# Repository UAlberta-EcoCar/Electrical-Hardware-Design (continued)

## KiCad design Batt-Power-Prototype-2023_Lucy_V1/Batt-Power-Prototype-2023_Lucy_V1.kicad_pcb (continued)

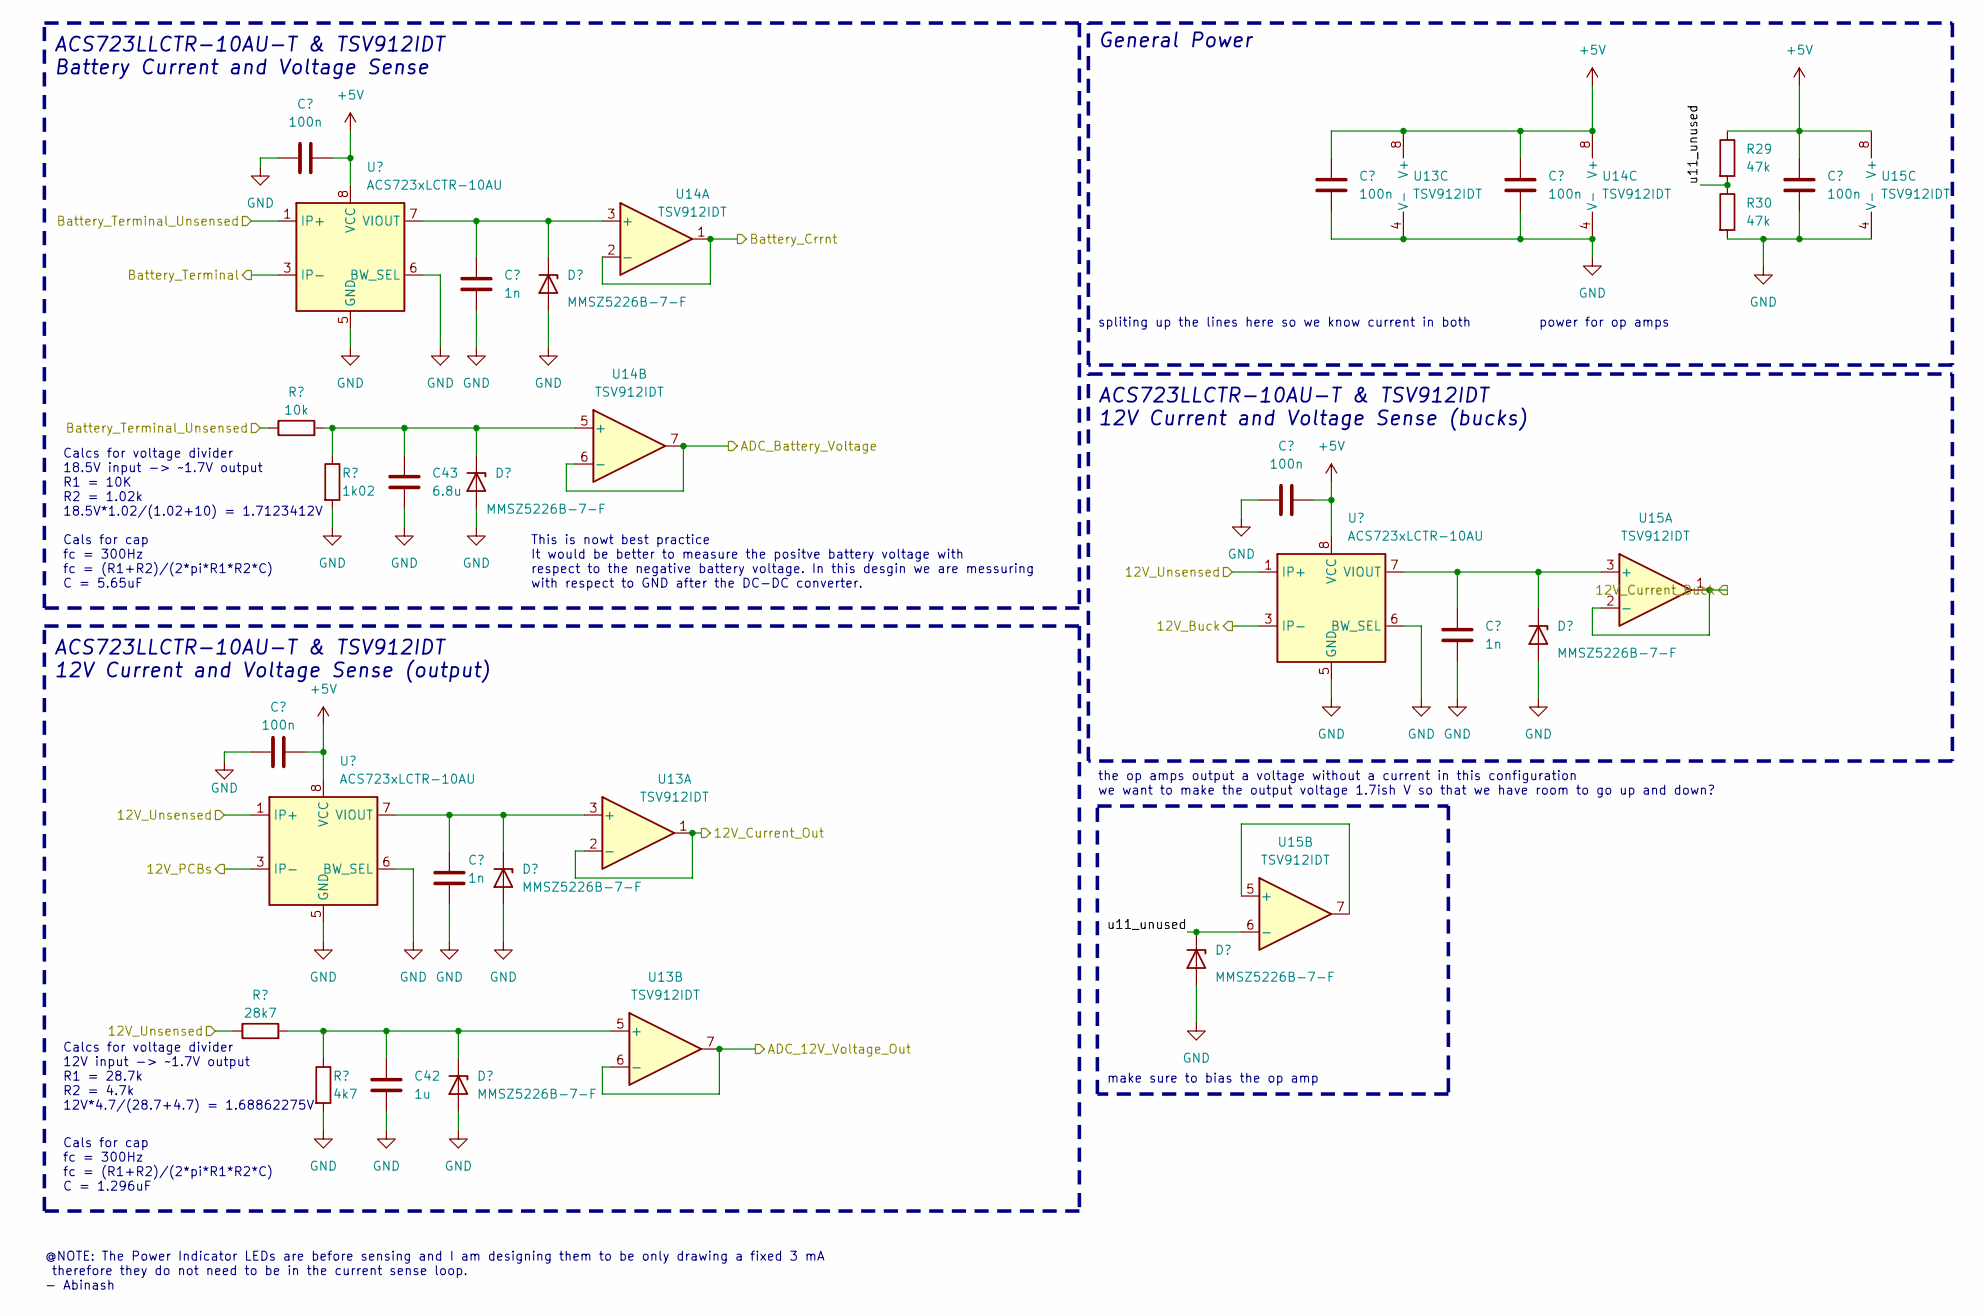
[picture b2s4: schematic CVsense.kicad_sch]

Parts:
C40, C46, C47, C49, C50: 100n; C_0603_1608Metric; Digikey # CC0603KRX7R7BB104
C41: 100n; C_0402_1005Metric; JLCPCB Part#(Optional) C1525
C42: 1u; C_0603_1608Metric; JLCPCB Part#(Optional) C28323
C43: 6.8u; C_0603_1608Metric; JLCPCB Part#(Optional) C1631
C44, C45, C48: 1n; C_0402_1005Metric; JLCPCB Part#(Optional) C1523
D16, D17, D18, D19, D20, D21: MMSZ5226B-7-F; D_SOD-123; Digikey # MMSZ5226B-FDICT-ND
R25: 28k7; R_0603_1608Metric; Digikey # RMCF0603FT28K7CT-ND
R26: 10k; R_0603_1608Metric; JLCPCB Part#(Optional) C25804
R27: 4k7; R_0603_1608Metric; JLCPCB Part#(Optional) C23164
R28: 1k02; R_0603_1608Metric; Digikey # RMCF0603FT1K02CT-ND
R29, R30: 47k; R_0805_2012Metric; JLCPCB Part#(Optional) C17713
U11, U12, U16: ACS723xLCTR-10AU; SOIC-8_3.9x4.9mm_P1.27mm
U13, U14, U15: TSV912IDT; SO8_STM; Digikey # 497-8165-2-ND

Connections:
+5V: C40.1, C41.2, C46.2, C47.1, C49.1, C50.1, R29.1, U11.8 (VCC), U12.8 (VCC), U13.8 (V+), U14.8 (V+), U15.8 (V+), U16.8 (VCC); also elsewhere on the board
/12V_Current_Buck: U15.1, U15.2 (-); also elsewhere on the board
/12V_Current_Out: U13.1, U13.2 (-); also elsewhere on the board
/ADC_12V_Voltage_Out: U13.6 (-), U13.7; also elsewhere on the board
/ADC_Battery_Voltage: U14.6 (-), U14.7; also elsewhere on the board
/Battery_Curr: U14.1, U14.2 (-); also elsewhere on the board
/Power/12V_Buck: U16.3 (IP-), U16.4 (IP-); also elsewhere on the board
/Power/12V_PCBs: U11.3 (IP-), U11.4 (IP-); also elsewhere on the board
/Power/12V_Unsensed: R25.1, U11.1 (IP+), U11.2 (IP+), U16.1 (IP+), U16.2 (IP+); also elsewhere on the board
/Power/Battery_Terminal_1: U12.3 (IP-), U12.4 (IP-); also elsewhere on the board
/Power/Battery_Terminal_1_Unsensed: R26.1, U12.1 (IP+), U12.2 (IP+); also elsewhere on the board
/Power/Current & Voltage Senseing/u11_unused: D20.1 (K), R29.2, R30.1, U15.6 (-)
GND: C40.2, C41.1, C42.2, C43.2, C44.2, C45.2, C46.1, C47.2, C48.2, C49.2, C50.2, D16.2 (A), D17.2 (A), D18.2 (A), D19.2 (A), D20.2 (A), D21.2 (A), R27.2, R28.2, R30.2, U11.5 (GND), U11.6 (BW_SEL), U12.5 (GND), U12.6 (BW_SEL), U13.4 (V-), U14.4 (V-), U15.4 (V-), U16.5 (GND), U16.6 (BW_SEL); also elsewhere on the board
unnamed: C42.1, D16.1 (K), R25.2, R27.1, U13.5 (+)
unnamed: C43.1, D17.1 (K), R26.2, R28.1, U14.5 (+)
unnamed: C44.1, D18.1 (K), U11.7 (VIOUT), U13.3 (+)
unnamed: C45.1, D19.1 (K), U12.7 (VIOUT), U14.3 (+)
unnamed: C48.1, D21.1 (K), U15.3 (+), U16.7 (VIOUT)
unnamed: U15.5 (+), U15.7

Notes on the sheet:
Cals for cap fc = 300Hz fc = (R1+R2)/(2*pi*R1*R2*C) C = 5.65uF
make sure to bias the op amp
the op amps output a voltage without a current in this configuration we want to make the output voltage 1.7ish V so that we have room to go up and down?
Calcs for voltage divider 12V input -> ~1.7V output R1 = 28.7k R2 = 4.7k 12V*4.7/(28.7+4.7) = 1.68862275V
General Power
ACS723LLCTR-10AU-T & TSV912IDT Battery Current and Voltage Sense
This is nowt best practice It would be better to measure the positve battery voltage with respect to the negative battery voltage. In this desgin we are messuring with respect to GND after the DC-DC converter.
Calcs for voltage divider 18.5V input -> ~1.7V output R1 = 10K R2 = 1.02k 18.5V*1.02/(1.02+10) = 1.7123412V
ACS723LLCTR-10AU-T & TSV912IDT 12V Current and Voltage Sense (output)
ACS723LLCTR-10AU-T & TSV912IDT 12V Current and Voltage Sense (bucks)
spliting up the lines here so we know current in both
power for op amps
Cals for cap fc = 300Hz fc = (R1+R2)/(2*pi*R1*R2*C) C = 1.296uF
@NOTE: The Power Indicator LEDs are before sensing and I am designing them to be only drawing a fixed 3 mA therefore they do not need to be in the current sense loop. - Abinash

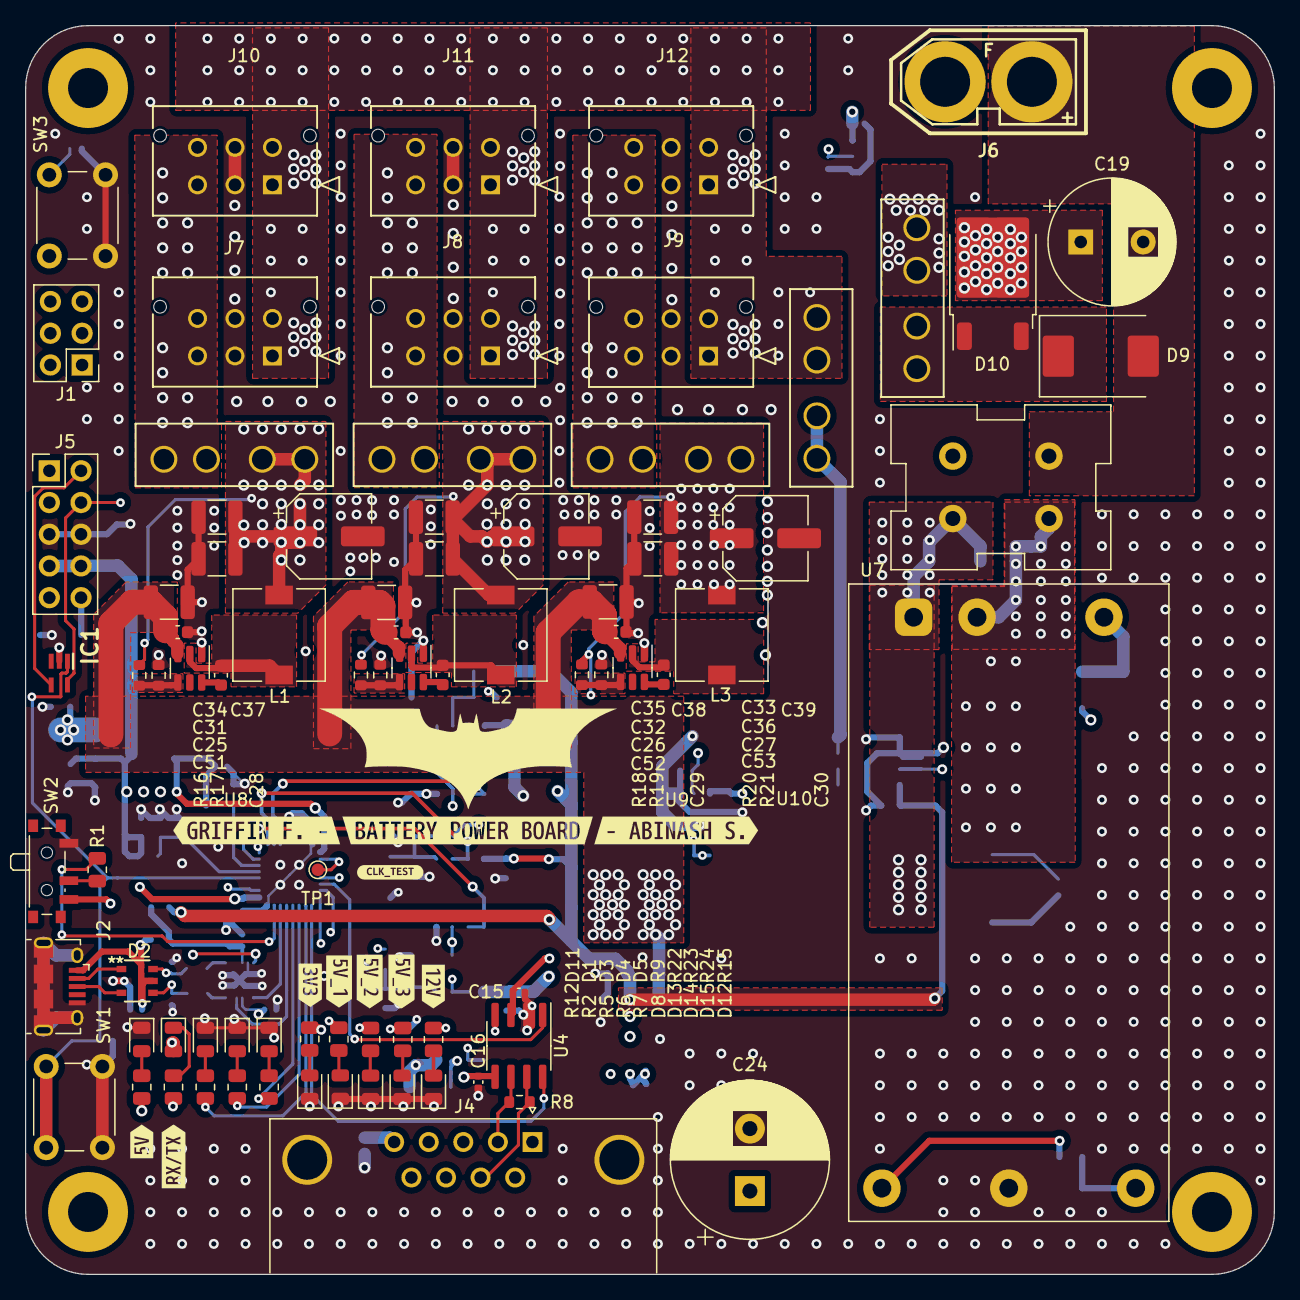
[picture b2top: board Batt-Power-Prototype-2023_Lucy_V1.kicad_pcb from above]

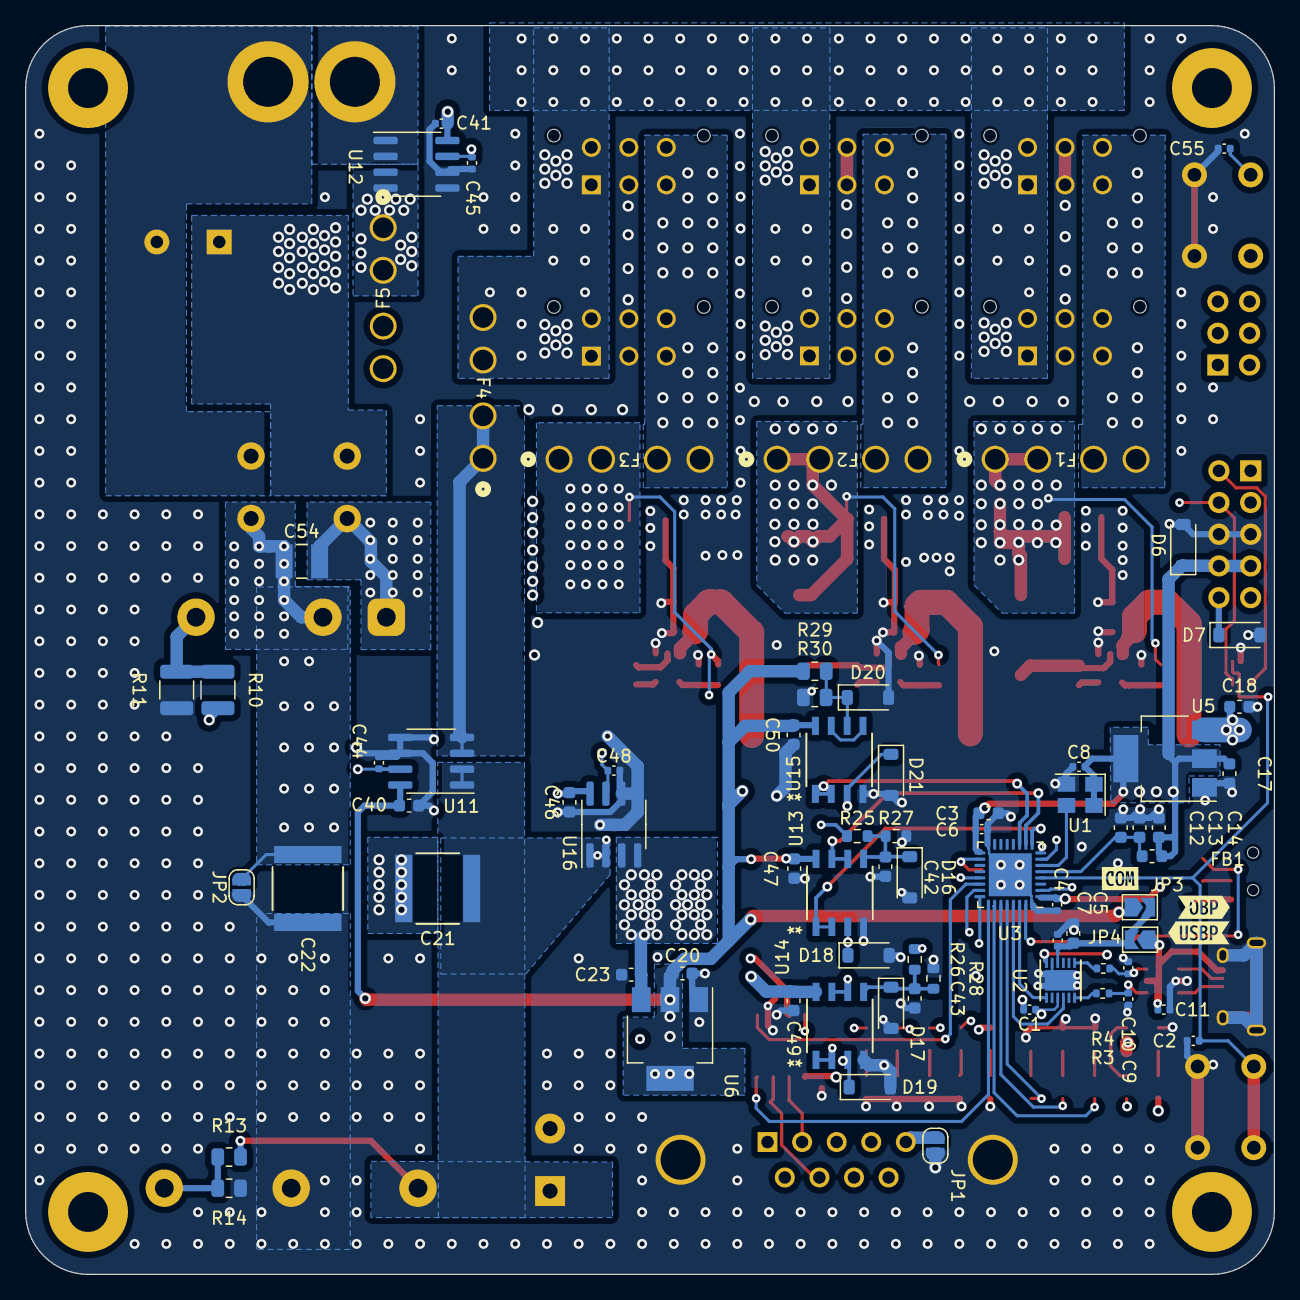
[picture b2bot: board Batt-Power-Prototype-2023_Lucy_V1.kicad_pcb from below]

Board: 4 copper layers, 100.0 x 100.0 mm, 170 parts (72 on the bottom side), 82 nets.

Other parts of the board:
kibuzzard-65BDD72B: G***; kibuzzard-65BDD72B
kibuzzard-65BDD721: G***; kibuzzard-65BDD721
kibuzzard-65BDD733: G***; kibuzzard-65BDD733
kibuzzard-65BDE8C6: G***; kibuzzard-65BDE8C6
kibuzzard-65BDE858: G***; kibuzzard-65BDE858
kibuzzard-65BDE861: G***; kibuzzard-65BDE861
kibuzzard-65BEF952: G***; kibuzzard-65BEF952
kibuzzard-65C1D3DC: G***; kibuzzard-65C1D3DC
kibuzzard-65C1D3E6: G***; kibuzzard-65C1D3E6
kibuzzard-65C1D3ED: G***; kibuzzard-65C1D3ED
kibuzzard-65C1D40B: G***; kibuzzard-65C1D40B
kibuzzard-65C1D405: G***; kibuzzard-65C1D405
kibuzzard-65C1D412: G***; kibuzzard-65C1D412
kibuzzard-65C1D419: G***; kibuzzard-65C1D419

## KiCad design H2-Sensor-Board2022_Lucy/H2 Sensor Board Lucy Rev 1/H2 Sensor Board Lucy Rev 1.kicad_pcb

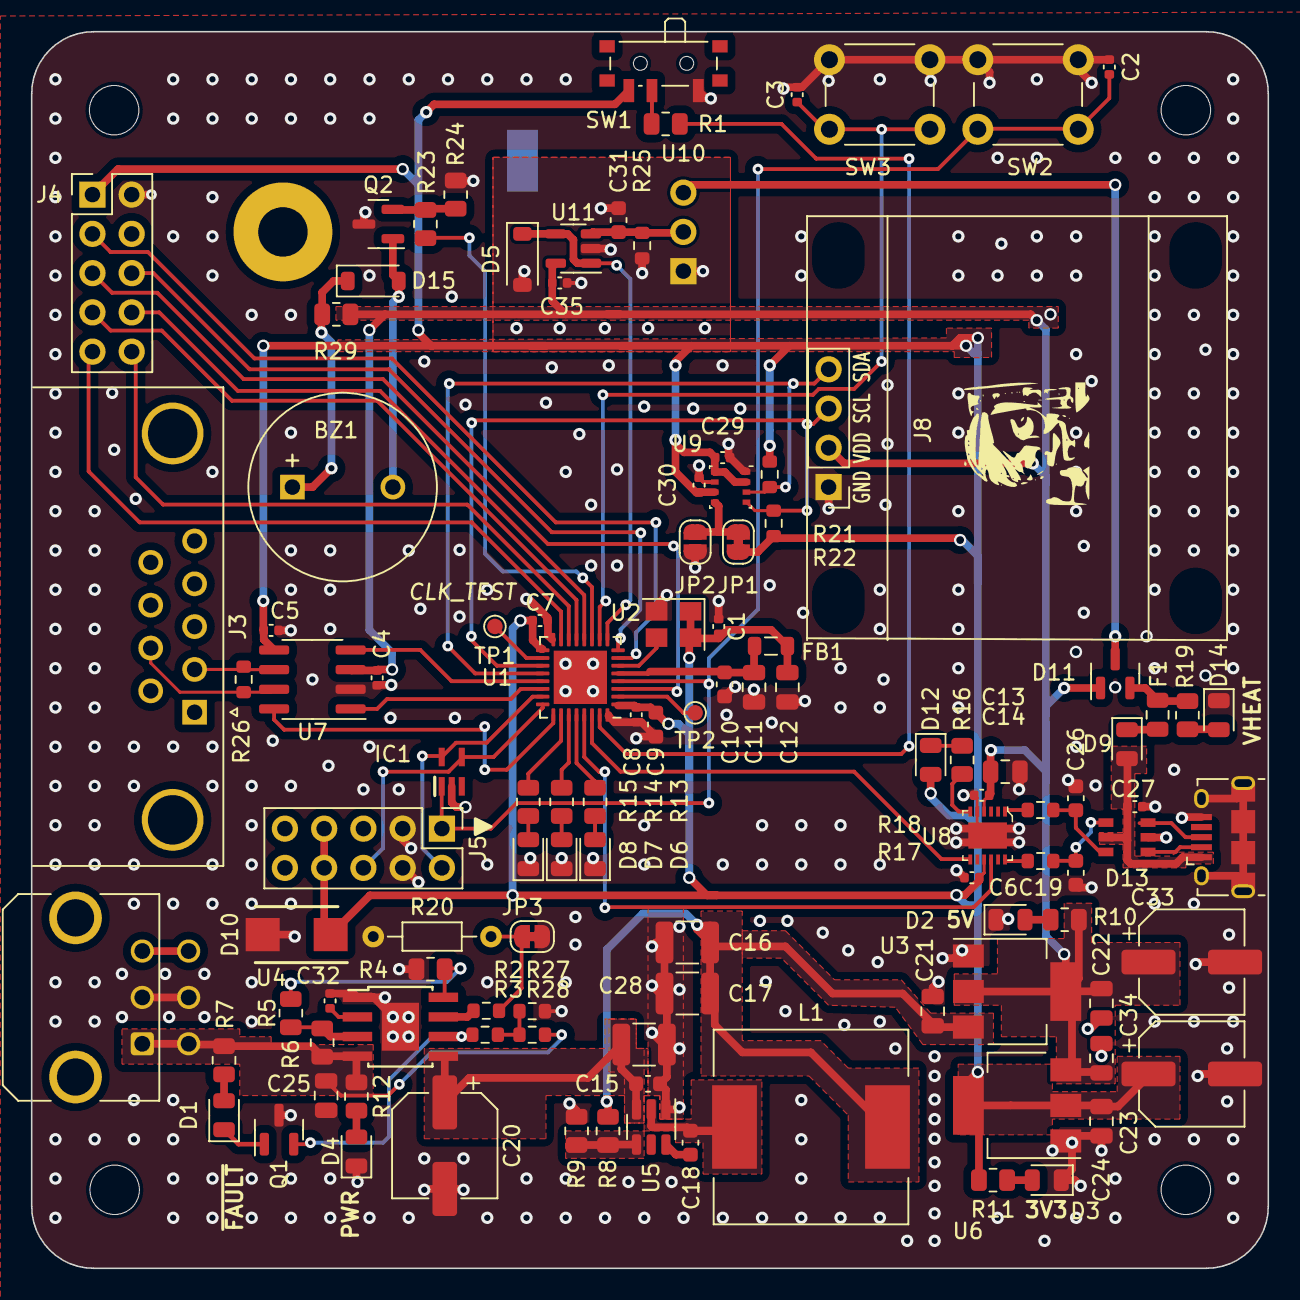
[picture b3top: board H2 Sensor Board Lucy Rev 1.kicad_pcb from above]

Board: 2 copper layers, 80.0 x 80.0 mm, 116 parts (1 on the bottom side), 75 nets.

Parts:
BZ1: Buzzer; MagneticBuzzer_ProSignal_ABT-410-RC
C1, C2, C3, C4, C5, C6, C7, C8, C14, C27, C29, C30, C35: 100n; C_0402_1005Metric
C9, C10: 10u; C_0603_1608Metric
C11, C12: 1u; C_0805_2012Metric
C13: 4u7; C_0805_2012Metric
C15, C18, C31: 100n; C_0603_1608Metric
C16, C17: 22u; C_1210_3225Metric
C19, C26: 47p; C_0603_1608Metric
C20: 100u; CP_Elec_6.3x5.9
C21, C23: 10u; C_0805_2012Metric
C22, C24: 22u; C_0805_2012Metric
C25: 100n; C_0805_2012Metric
C28: 10u; C_1210_3225Metric
C32: 2n2; C_0402_1005Metric
C33, C34: 22u; CP_Elec_6.3x5.9
D1, D6: GREEN; LED_0805_2012Metric
D2, D3, D4, D14: BLUE; LED_0805_2012Metric
D5: MMSZ5226B-7-F; D_SOD-123
D7: RED; LED_0805_2012Metric
D8, D12: AMBER; LED_0805_2012Metric
D9: D_Schottky; D_0805_2012Metric
D10: SMLVT3V3; DIOM5436X265N
D11: BAT54C; SOT-23
D13: USBLC6-2SC6; SOT23-6L_STM
D15: BAV16W/1N4148W; D_SOD-123
F1: 500mA; Fuse_0805_2012Metric
FB1: 300R; L_0805_2012Metric
H1, H2, H3, H4: MountingHole; MountingHole_3.2mm_M3
IC1: ESDALC6V1W5; SOT65P210X110-5N
J2: Conn_02x03_Top_Bottom; Molex_Micro-Fit_3.0_43045-0621_2x03-1MP_P3.00mm_Horizontal
J3: Conn_01x09_Socket; DSUB-9_Female_Horizontal_P2.77x2.84mm_EdgePinOffset7.70mm_H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
J4: GPIO; PinHeader_2x05_P2.54mm_Vertical
J5: Conn_02x05_Top_Bottom; PinHeader_2x05_P2.54mm_Vertical
J6: USB_B_Micro; USB_Micro-B_Amphenol_10118194_Horizontal
J8: OLED; Display_128x64_096_I2C
JP1: Slave Address LSB 1; SolderJumper-2_P1.3mm_Bridged_RoundedPad1.0x1.5mm
JP2: Slave Address LSB 0; SolderJumper-2_P1.3mm_Open_RoundedPad1.0x1.5mm
JP3: MAX CURRENT; SolderJumper-2_P1.3mm_Bridged_RoundedPad1.0x1.5mm
L1: 3u8; L_12x12mm_H8mm
NT1: NetTie_2; NetTie-2_SMD_Pad2.0mm
Q1: NMOS; SOT-23
Q2: NMOS IRLML2502TRPBF; SOT-23
R1, R24: 10k; R_0805_2012Metric
R2: 620R; R_0603_1608Metric
R3, R21, R22, R25: 4k7; R_0603_1608Metric
R4, R8: 47k; R_0805_2012Metric
R5: 15; R_0805_2012Metric
R6: 470k; R_0805_2012Metric
R7, R12: 2k; R_0805_2012Metric
R9: 6k2; R_0805_2012Metric
R10, R19: 560R; R_0805_2012Metric
R11, R13, R14, R15, R16: 220R; R_0805_2012Metric
R17, R18: 27R; R_0603_1608Metric
R20: R; R_Axial_DIN0204_L3.6mm_D1.6mm_P7.62mm_Horizontal
R23: 10R; R_0805_2012Metric
R26: 120R; R_0603_1608Metric
R27: 30k; R_0603_1608Metric
R28: 47k; R_0603_1608Metric
R29: 1k; R_0805_2012Metric
SW1: SW_SPDT; SW_SPDT_PCM12
SW2: RESET; SW_PUSH_6mm_H5mm
SW3: TARE; SW_PUSH_6mm_H5mm
TP1: MCO; TestPoint_Pad_D1.0mm
TP2: GPTP; TestPoint_Pad_D1.0mm
U1: STM32L432KCU6; QFN-32-1EP_5x5mm_P0.5mm_EP3.45x3.45mm
U2: 8MHz; Crystal_SMD_3225-4Pin_3.2x2.5mm
U3: AZ1117IH-5.0; SOT-223-3_TabPin2
U4: TPS2596; TI_SO-PowerPAD-8
U5: AP62250; TSOT-23-6
U6: AZ1117IH-3.3; SOT-223-3_TabPin2
U7: MCP2542FD-E/SN; SOIC-8_3.9x4.9mm_P1.27mm
U8: FT234XD-R; DFN-12-1EP_3x3mm
U9: BME280; Bosch_LGA-8_2.5x2.5mm_P0.65mm_ClockwisePinNumbering
U10: H2_Sensor_Daughter_Board_Rev_1
U11: AD8603; TSOT-23-5

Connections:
+3.3VA: C10.1, C11.1, FB1.1, U1.5 (VDDA)
+3V3: C1.2, C5.2, C6.1, C7.1, C8.1, C9.1, C12.1, C24.1, C29.1, C30.1, C34.1, D10.1 (K), D12.2 (A), FB1.2, J4.1, J5.7, J5.8, JP1.2 (B), R11.1, R21.1, R22.1, SW1.3 (C), U1.1 (VDD), U1.17 (VDD), U2.1 (~ST), U2.4 (VCC), U6.2 (VO), U7.5 (VIO), U8.9 (VCCIO), U9.2 (CSB), U9.6 (VDDIO), U9.8 (VDD)
+5V: C4.2, C13.1, C14.1, C22.1, C23.1, C33.1, C35.1, D11.1, J8.2, R10.1, R29.1, U3.2 (VO), U6.3 (VI), U7.3 (VDD), U8.4 (VCC), U11.5 (V+)
+12V: C15.1, C20.1, C28.1, U4.5 (OUT), U5.3 (VIN)
/BEEPER: R23.2, U1.11 (PA5)
/BOOT0: R1.2, U1.31 (PH3)
/CAN_RX: U1.21 (PA11), U7.4 (RXD)
/CAN_STBY: U1.25 (PA15), U7.8 (STBY)
/CAN_TX: U1.22 (PA12), U7.1 (TXD)
/CD+: J3.7, R26.1, U7.7 (CANH)
/CD-: J3.2, R26.2, U7.6 (CANL)
/DEBUG_SWCLK: IC1.4 (I/03), J5.6, U1.24 (PA14)
/DEBUG_SWDIO: IC1.5 (I/04), J5.2, U1.23 (PA13)
/GPIO1: J4.8, U1.12 (PA6)
/GPIO2: J4.10, U1.14 (PB0)
/GPIO3: J4.5, U1.3 (PC15)
/GPIO4: J4.6, U1.8 (PA2)
/GPIO7: J4.9, U1.15 (PB1)
/GPIO8: J4.7, U1.13 (PA7)
/GPIO9: J4.3, U1.7 (PA1)
/GPLED1: R15.2, U1.26 (PB3)
/GPLED2: R14.2, U1.27 (PB4)
/GPLED3: R13.2, U1.28 (PB5)
/H2_SENSE: D5.1 (K), U1.9 (PA3), U11.1, U11.4 (-)
/NRST: C2.2, IC1.1 (I/01), J5.1, SW2.2, U1.4 (NRST)
/Power/5V_UP: J2.3, J2.6
/Power/7V: C16.1, C17.1, C21.1, L1.2, R8.1, U3.3 (VI)
/Power/12V_UP: C25.1, J2.1, J2.4, R6.2, R7.1, R12.1, R28.1, U4.4 (IN)
/Power/FB: R8.2, R9.2, U5.4 (FB)
/Power/I_{MON}: R2.1, U4.7 (ILM)
/Power/SW: C18.1, L1.1, U5.2 (SW)
/Power/~FAULT: Q1.2 (G), R3.1, U4.6 (~FAULT)
/SCL: J8.3, R22.2, U1.19 (PA9), U9.4 (SCK)
/SDA: J8.4, R21.2, U1.20 (PA10), U9.3 (SDI)
/Sensors/ADDR: JP1.1 (A), JP2.1 (A), U9.5 (SDO)
/Sensors/V_SENSE: C31.1, R25.2, U10.2 (V_SENSE), U11.3 (+)
/TARE: C3.2, SW3.2, U1.10 (PA4)
/UART_RX: U1.30 (PB7), U8.7 (TXD)
/UART_TX: U1.29 (PB6), U8.10 (RXD)
/XCLK: U1.6 (PA0), U2.3 (OUT)
GND: C1.1, C2.1, C3.1, C4.1, C5.1, C6.2, C7.2, C8.2, C9.2, C10.2, C11.2, C12.2, C13.2, C14.2, C15.2, C16.2, C17.2, C19.1, C20.2, C21.2, C22.2, C23.2, C24.2, C25.2, C26.1, C27.1, C28.2, C29.2, C30.2, C32.2, C33.2, C34.2, D2.1 (K), D3.1 (K), D4.1 (K), D6.1 (K), D7.1 (K), D8.1 (K), D10.2 (A), D13.2, D14.1 (K), IC1.2 (GND), J2.2, J2.5, J4.2, J5.3, J5.4, J6.5 (GND), J6.6 (Shield), J8.1, JP2.2 (B), JP3.2 (B), NT1.2, Q1.3 (S), Q2.3 (S), R4.2, R9.1, R20.1, R24.2, R27.1, SW1.1 (A), SW2.1, SW3.1, U1.16 (VSS), U1.32 (VSS), U1.33 (VSS), U2.2 (GND), U3.1 (GND), U4.1 (GND), U4.9 (PAD), U5.1 (GND), U6.1 (GND), U7.2 (VSS), U8.5 (GND), U8.13 (GND), U9.1 (GND), U9.7 (GND)
GNDA: C31.2, C35.2, D5.2 (A), NT1.1, R25.1, U10.1 (GND), U11.2 (V-)
unnamed: BZ1.2 (+), D15.2 (A), Q2.1 (D)
unnamed: BZ1.1 (-), D15.1 (K), R29.2
unnamed: C19.2, D13.4, R17.2
unnamed: C26.2, D13.6, R18.2
unnamed: D1.2 (A), R7.2
unnamed: D1.1 (K), Q1.1 (D)
unnamed: D2.2 (A), R10.2
unnamed: D3.2 (A), R11.2
unnamed: D4.2 (A), R12.2
unnamed: D6.2 (A), R13.1
unnamed: D7.2 (A), R14.1
unnamed: D8.2 (A), R15.1
unnamed: D9.1 (K), F1.1
unnamed: D12.1 (K), R16.2
unnamed: D14.2 (A), R19.2
unnamed: D13.3, J6.3 (D+)
unnamed: D13.1, J6.2 (D-)
unnamed: JP3.1 (A), R2.2, R20.2
unnamed: Q2.2 (G), R23.1, R24.1
unnamed: R3.2, R27.2, R28.2
unnamed: R1.1, SW1.2 (B)
unnamed: TP1.1, U1.18 (PA8)
unnamed: TP2.1, U1.2 (PC14)
unnamed: R5.1, R6.1, U4.3 (EN/UVLO)
unnamed: R4.1, R5.2, U4.8 (OVLO)
unnamed: C32.1, U4.2 (dV/dT)
unnamed: C18.2, U5.6 (BST)
unnamed: R16.1, U8.6 (CBUS0)
unnamed: R18.1, U8.1 (USBDM)
unnamed: R17.1, U8.12 (USBDP)
unnamed: D11.3, U10.3 (V_HEAT)
VBUS_UP: C27.2, D9.2 (A), D13.5, J6.1 (VBUS)
V_HEAT: D11.2, F1.2, R19.1

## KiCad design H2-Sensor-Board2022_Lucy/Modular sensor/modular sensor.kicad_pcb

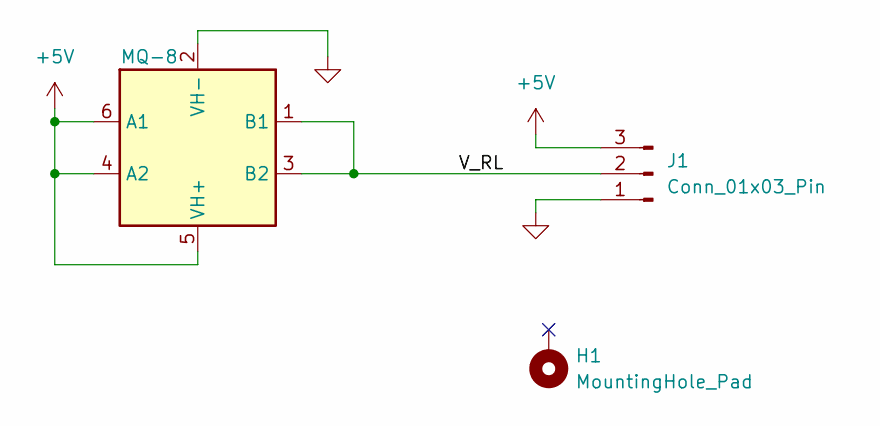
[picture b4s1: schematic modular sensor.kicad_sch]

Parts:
H1: MountingHole_Pad; MountingHole_3.2mm_M3_Pad
J1: Conn_01x03_Pin; PinHeader_1x03_P2.54mm_Vertical; LCSC C49257
MQ-8: MQ-8

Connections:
+5V: J1.3, MQ-8.4 (A2), MQ-8.5 (VH+), MQ-8.6 (A1)
/V_RL: J1.2, MQ-8.1 (B1), MQ-8.3 (B2)
GND: J1.1, MQ-8.2 (VH-)

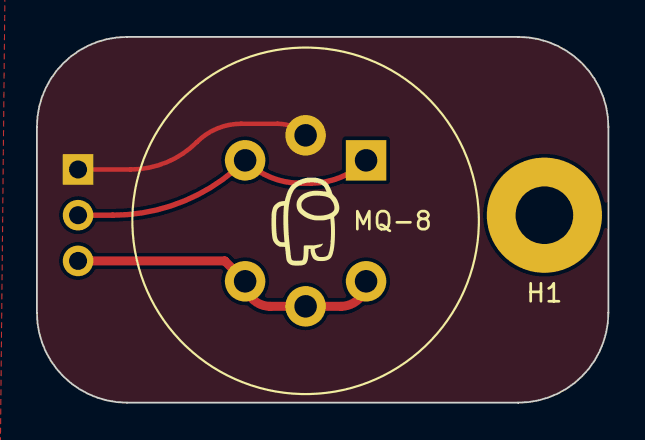
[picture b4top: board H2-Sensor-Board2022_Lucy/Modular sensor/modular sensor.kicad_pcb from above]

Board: 2 copper layers, 31.8 x 20.3 mm, 3 parts (1 on the bottom side), 3 nets.

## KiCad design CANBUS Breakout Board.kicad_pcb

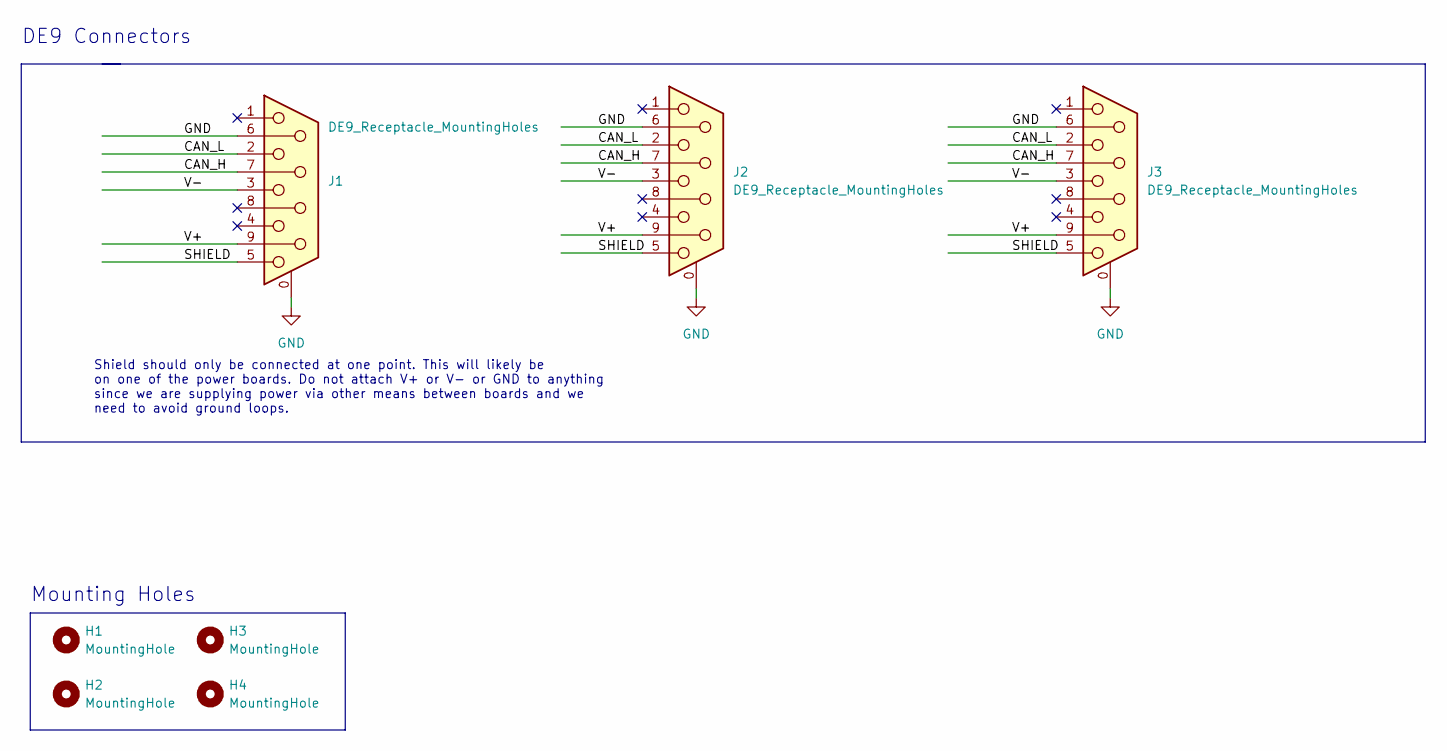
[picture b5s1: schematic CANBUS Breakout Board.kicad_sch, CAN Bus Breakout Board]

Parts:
H1, H2, H3, H4: MountingHole; MountingHole_2.2mm_M2
J1, J2, J3: DE9_Receptacle_MountingHoles; DSUB-9_Female_Vertical_P2.77x2.84mm_MountingHoles

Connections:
/CAN_H: J1.7, J2.7, J3.7
/CAN_L: J1.2, J2.2, J3.2
/SHIELD: J1.5, J2.5, J3.5
/V+: J1.9, J2.9, J3.9
/V-: J1.3, J2.3, J3.3
GND: J1.0 (PAD), J1.6, J2.0 (PAD), J2.6, J3.0 (PAD), J3.6

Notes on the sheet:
Mounting Holes
Shield should only be connected at one point. This will likely be on one of the power boards. Do not attach V+ or V- or GND to anything since we are supplying power via other means between boards and we need to avoid ground loops.
DE9 Connectors

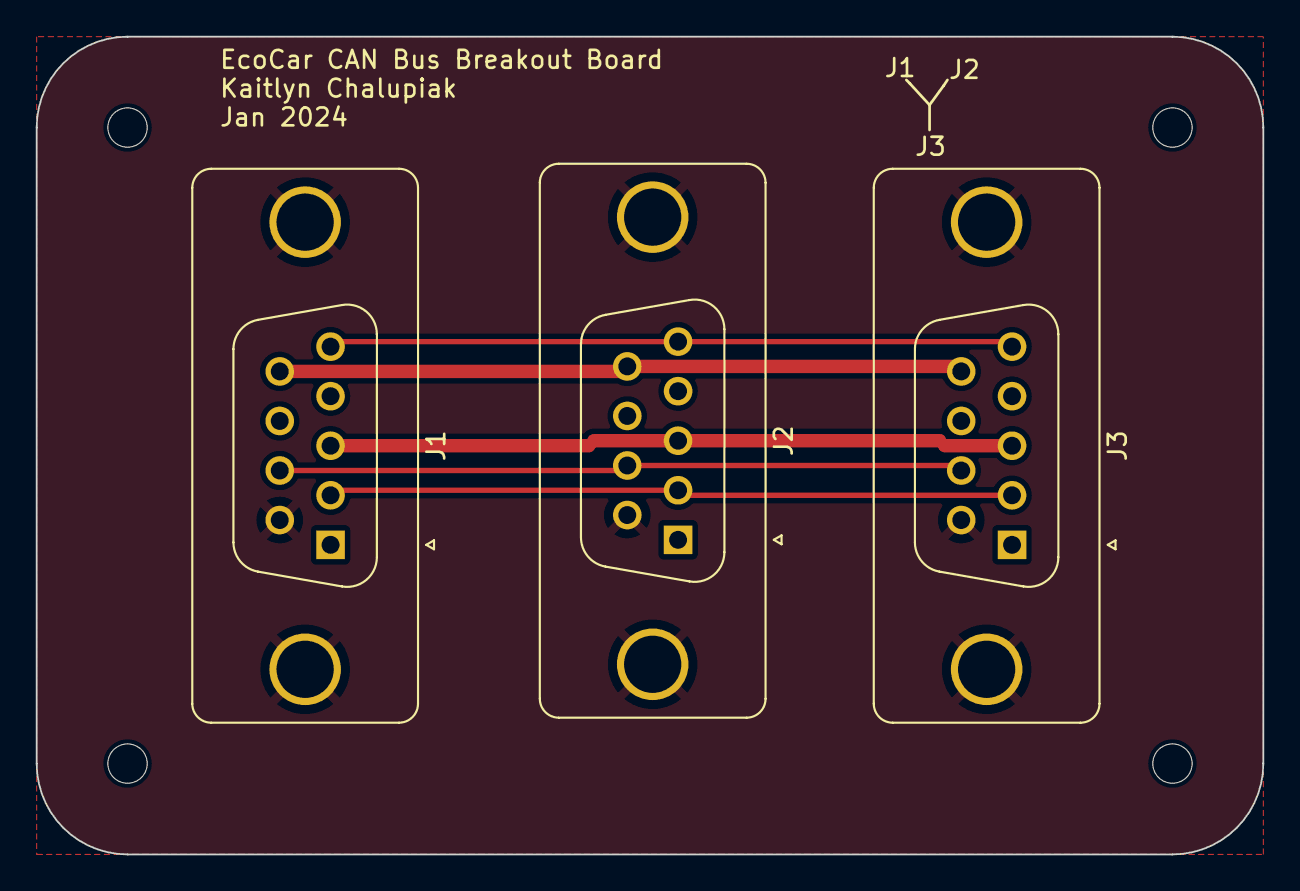
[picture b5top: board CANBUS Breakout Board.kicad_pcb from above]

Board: 2 copper layers, 68.6 x 45.7 mm, 7 parts (0 on the bottom side), 6 nets.
